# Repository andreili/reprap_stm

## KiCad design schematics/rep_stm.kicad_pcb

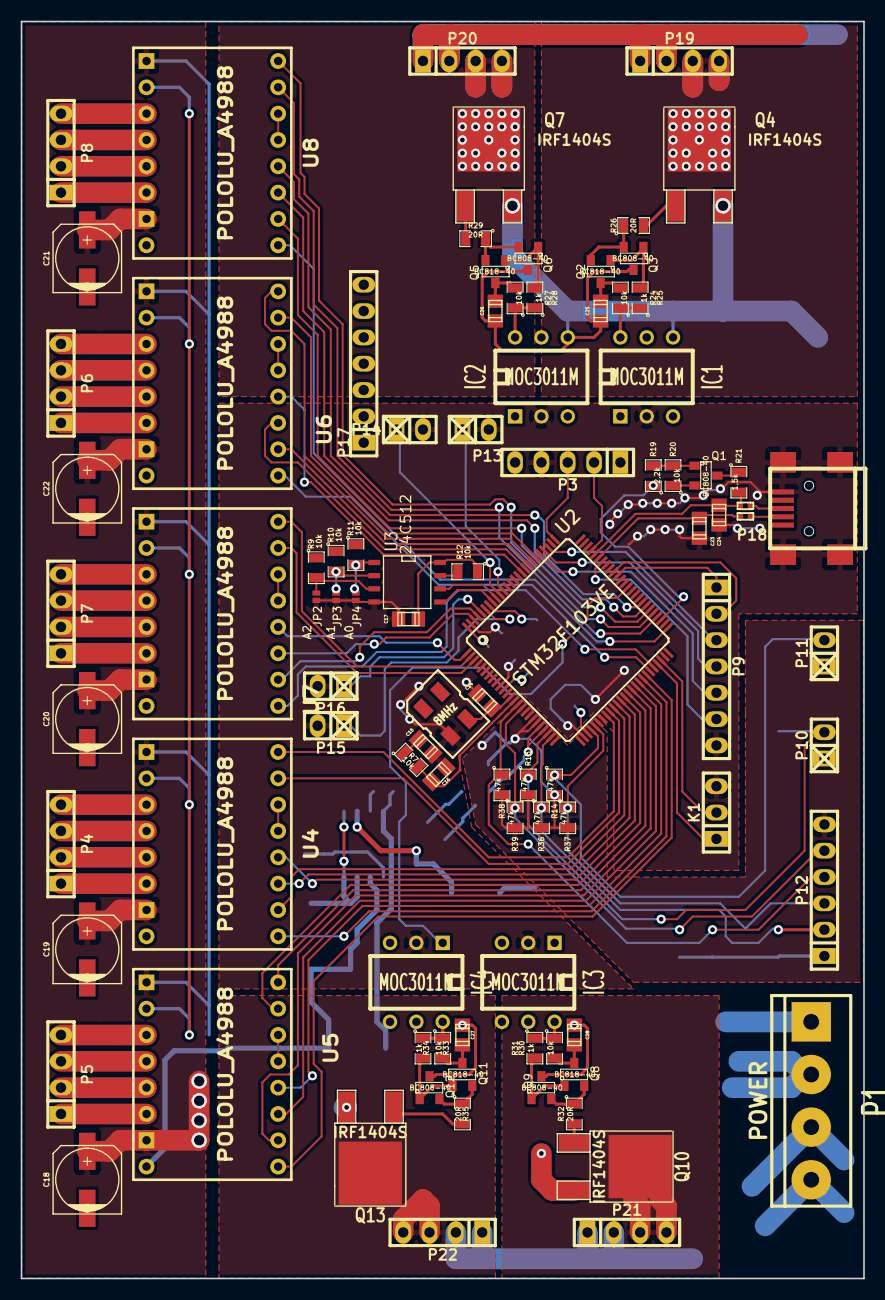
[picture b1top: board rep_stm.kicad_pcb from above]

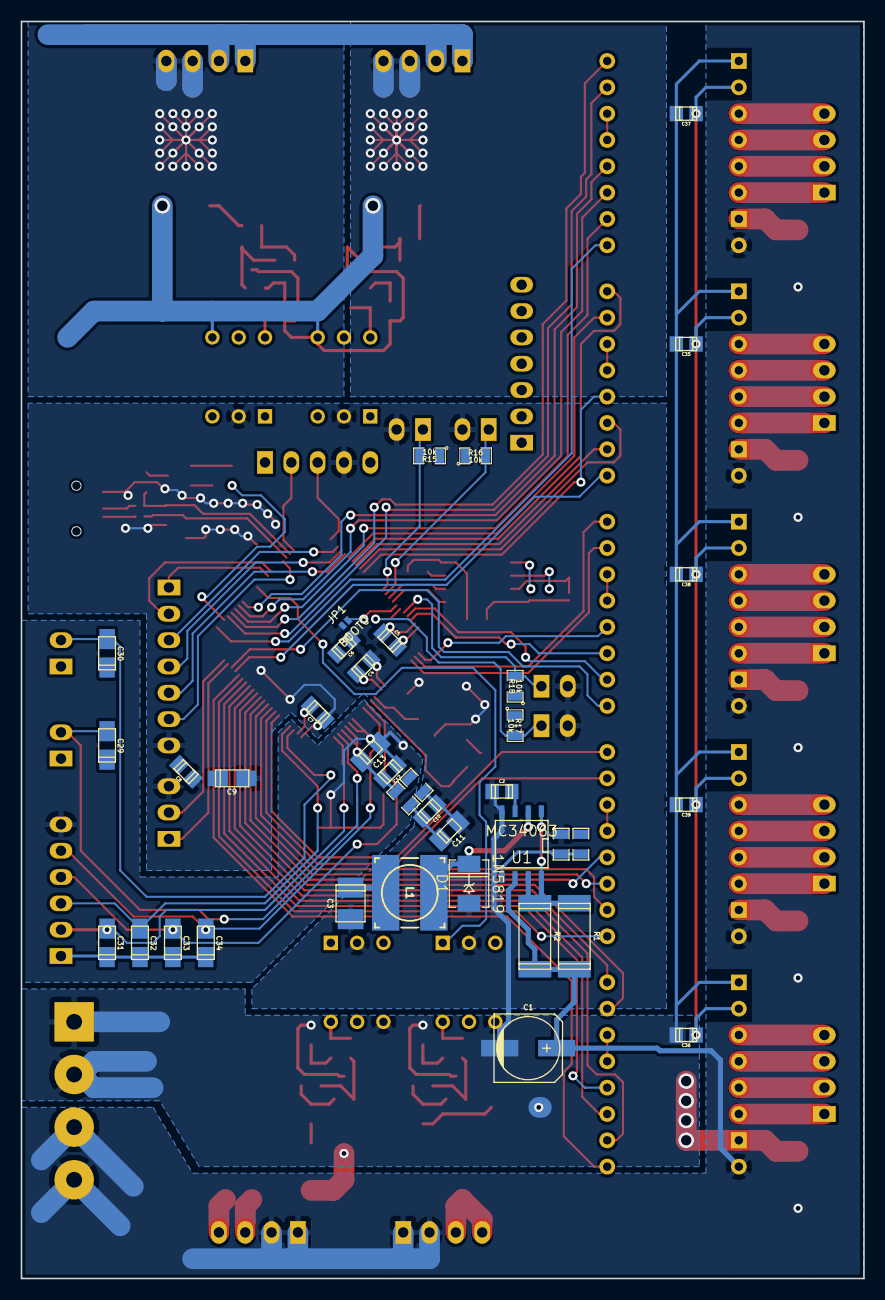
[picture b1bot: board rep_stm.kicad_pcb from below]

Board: 2 copper layers, 81.3 x 121.3 mm, 131 parts (38 on the bottom side), 129 nets.

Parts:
C1: 100u; c_elec_6.3x7.7
C2: 150pF; c_0805
C3: 47uF; c_tant_B
C4, C5, C6, C7, C8, C16, C17, C35, C36, C37, C38, C39: 100n; c_0805
C9: 4,7uF; c_tant_A
C10, C12, C15, C25, C26, C27, C28: 10n; c_0805
C11, C13: 1uF; c_tant_R
C14, C23, C24: 22pF; c_0805
C18, C19, C20, C21, C22: 100uFx25V; c_elec_6.3x7.7
C29, C30, C31, C32, C33, C34: 10uF; c_tant_A
D1: 1N5819; DO-214AC(SMA)
IC1, IC2, IC3, IC4: MOC3011M; DIP-6__300
JP1: BOOT0; S_JUMPER_2
JP2: A2; S_JUMPER_2
JP3: A1; S_JUMPER_2
JP4: A0; S_JUMPER_2
K1: UART; pin_socket_3
L1: 22uH; Inductor_CDRH6D28
L2, L3: 10uH; SM0805_Opendous
P1: POWER; bornier4
P3: PROG; pin_socket_5
P4: DRIVE 1; pin_socket_4
P5: DRIVE 2; pin_socket_4
P6: DRIVE 3; pin_socket_4
P7: DRIVE 4; pin_socket_4
P8: DRIVE 5; pin_socket_4
P9: DIGITAL OUT; pin_socket_7
P10: THERM1; pin_socket_2
P11: THERM2; pin_socket_2
P12: ANALOG IN; pin_socket_6
P13: END1; pin_socket_2
P14: END2; pin_socket_2
P15: END3; pin_socket_2
P16: END4; pin_socket_2
P17: DIGITAL INP; pin_socket_7
P18: USB-MINI-B; USB_MINI_B
P19: PWM 1; pin_socket_4
P20: PWM 2; pin_socket_4
P21: PWM 3; pin_socket_4
P22: PWM 4; pin_socket_4
Q1, Q3, Q6, Q9, Q12: BC808-40; SOT23
Q2, Q5, Q8, Q11: BC818-40; SOT23
Q4, Q7, Q10, Q13: IRF1404S; DPAK2
R1, R2: 0,47; r_2512
R5: 1,2k; SM0805_Opendous
R6: 2k; SM0805_Opendous
R7, R9, R10, R11, R12, R15, R16, R17, R18, R20, R24, R27, R30, R33: 10k; SM0805
R13, R14, R36, R37, R38, R39: 47k; SM0805
R19: 2,2k; SM0805
R21: 1,5k; SM0805
R22, R23: 33R; SM0402_Opendous
R25, R28, R31, R34: 1k; SM0805
R26, R29, R32, R35: 20R; SM0805
U1: MC34063; SO8N
U2: STM32F103VE; LQFP100
U3: 24C512; SO8N
U4, U5, U6, U7, U8: POLOLU_A4988; SWDIP8_.6W
X1: 8MHz; Crystal_7x5mm

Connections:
+12V: C1.1, C18.2, C19.2, C20.2, C21.2, C22.2, C25.1, C26.1, C27.1, C28.1, P1.3, P1.4, P19.1, P19.2, P20.1, P20.2, P21.1, P21.2, P22.1, P22.2, Q2.3, Q5.3, Q8.3, Q11.3, R1.1, R2.1, R24.2, R27.2, R30.2, R33.2, U1.6, U4.8, U5.8, U6.8, U7.8, U8.8
AIN1: C29.2, P10.2, R13.1, U2.23
AIN2: C31.2, P12.2, R36.1, U2.24
AIN3: C30.2, P11.2, R14.1, U2.29
AIN4: C32.2, P12.3, R37.1, U2.30
AIN5: C33.2, P12.4, R38.1, U2.15
AIN6: C34.2, P12.5, R39.1, U2.16
BOOT0: JP1.2, U2.94
DM: C23.1, R22.1, U2.70
DP: C24.1, R21.2, R23.1, U2.71
DR4MS2: U2.1, U7.12
Dr1Dir: U2.33, U4.16
Dr1Enable: U2.43, U4.9
Dr1MS0: U2.35, U4.10
Dr1MS1: U2.36, U4.11
Dr1MS2: U2.37, U4.12
Dr1Step: U2.34, U4.15
Dr2Dir: U2.39, U5.16
Dr2Enable: U2.44, U5.9
Dr2MS0: U2.40, U5.10
Dr2MS1: U2.41, U5.11
Dr2MS2: U2.42, U5.12
Dr2Step: U2.38, U5.15
Dr3Dir: U2.82, U6.16
Dr3Enable: U2.45, U6.9
Dr3MS0: U2.83, U6.10
Dr3MS1: U2.84, U6.11
Dr3MS2: U2.85, U6.12
Dr3Step: U2.81, U6.15
Dr4Dir: U2.2, U7.16
Dr4Enable: U2.46, U7.9
Dr4MS0: U2.97, U7.10
Dr4MS1: U2.98, U7.11
Dr4Step: U2.3, U7.15
Dr5Dir: U2.55, U8.16
Dr5Enable: U2.51, U8.9
Dr5MS0: U2.56, U8.10
Dr5MS1: U2.57, U8.11
Dr5MS2: U2.58, U8.12
Dr5Step: U2.54, U8.15
I2C_SCL: U2.92, U3.6
I2C_SDA: U2.93, U3.5
IN1: P13.1, R15.2, U2.90
IN2: P14.1, R16.2, U2.91
IN3: P15.1, R17.2, U2.95
IN4: P16.1, R18.2, U2.96
IN6: P17.2, U2.88
IN7: P17.3, U2.4, U2.17
IN8: P17.4, U2.5, U2.18
IN9: P17.5, U2.25
IN10: P17.6, U2.26
unnamed: JP4.2, R11.2, U3.1
unnamed: JP2.2, R9.2, U3.3
unnamed: JP3.2, R10.2, U3.2
unnamed: U8.13, U8.14
unnamed: U7.13, U7.14
unnamed: U6.13, U6.14
unnamed: R12.2, U3.7
unnamed: Q1.1, R19.2, R20.2
unnamed: U5.13, U5.14
unnamed: U4.13, U4.14
unnamed: Q10.1, R32.2
unnamed: Q13.1, R35.2
unnamed: Q8.1, Q9.1, R31.2
unnamed: R1.2, R2.2, U1.1, U1.7, U1.8
unnamed: C2.1, U1.3
unnamed: Q5.2, Q6.2, R29.1
unnamed: P6.4, U6.3
unnamed: P6.3, U6.4
unnamed: P5.1, U5.6
unnamed: P5.2, U5.5
unnamed: P5.3, U5.4
unnamed: P5.4, U5.3
unnamed: P7.1, U7.6
unnamed: P7.2, U7.5
unnamed: P7.3, U7.4
unnamed: P7.4, U7.3
unnamed: P6.1, U6.6
unnamed: P6.2, U6.5
unnamed: P4.1, U4.6
unnamed: P4.2, U4.5
unnamed: P4.3, U4.4
unnamed: P4.4, U4.3
unnamed: P8.1, U8.6
unnamed: P8.2, U8.5
unnamed: P8.3, U8.4
unnamed: P8.4, U8.3
unnamed: Q8.2, Q9.2, R32.1
unnamed: IC4.6, R33.1, R34.1
unnamed: Q11.1, Q12.1, R34.2
unnamed: IC3.6, R30.1, R31.1
unnamed: Q2.2, Q3.2, R26.1
unnamed: IC2.6, R27.1, R28.1
unnamed: Q5.1, Q6.1, R28.2
unnamed: Q11.2, Q12.2, R35.1
unnamed: IC1.6, R24.1, R25.1
unnamed: Q2.1, Q3.1, R25.2
unnamed: D1.2, L1.1, U1.2
unnamed: R5.1, R6.1, U1.5
unnamed: Q7.1, R29.2
unnamed: P18.3, R23.2
unnamed: P18.2, R22.2
unnamed: Q1.3, R21.1
unnamed: Q4.1, R26.2
NRST: C16.1, P3.1, R7.2, U2.14
OSC_OUT: C14.1, U2.13, X1.3
OUT1: P9.1, U2.65
OUT2: P9.2, U2.66
OUT3: P9.3, U2.78
OUT4: P9.4, U2.79
OUT5: P9.5, U2.80
OUT6: P9.6, U2.69
PWM1: IC1.1, U2.59
PWM1OUT: P19.3, P19.4, Q4.2
PWM2: IC2.1, U2.60
PWM2OUT: P20.3, P20.4, Q7.2
PWM3: IC3.1, U2.61
PWM3OUT: P21.3, P21.4, Q10.2
PWM4: IC4.1, U2.62
PWM4OUT: P22.3, P22.4, Q13.2
SWCLK: P3.3, U2.76
SWDIO: P3.2, U2.72
SlaveRX: K1.2, U2.48
SlaveTX: K1.1, U2.47
USBEN: R19.1, U2.53
VCOM: C1.2, C2.2, C3.2, C4.2, C5.2, C6.2, C7.2, C8.2, C9.2, C10.2, C11.2, C14.2, C15.2, C16.2, C17.2, C18.1, C19.1, C20.1, C21.1, C22.1, C23.2, C24.2, C25.2, C26.2, C27.2, C28.2, C35.1, C36.1, C37.1, C38.1, C39.1, D1.1, IC1.2, IC1.4, IC2.2, IC2.4, IC3.2, IC3.4, IC4.2, IC4.4, JP1.1, JP2.1, JP3.1, JP4.1, K1.3, L3.1, P1.1, P1.2, P3.4, P9.7, P13.2, P14.2, P15.2, P16.2, P17.7, P18.5, P18.6, P18.7, P18.8, P18.9, Q3.3, Q4.3, Q6.3, Q7.3, Q9.3, Q10.3, Q12.3, Q13.3, R5.2, U1.4, U2.10, U2.27, U2.49, U2.74, U2.99, U3.4, U4.1, U4.7, U5.1, U5.7, U6.1, U6.7, U7.1, U7.7, U8.1, U8.7, X1.2
VDD: C3.1, C4.1, C5.1, C6.1, C7.1, C8.1, C9.1, C10.1, C11.1, C15.1, C17.1, C35.2, C36.2, C37.2, C38.2, C39.2, L1.2, L2.1, P3.5, Q1.2, R6.2, R7.1, R9.1, R10.1, R11.1, R12.1, R15.1, R16.1, R17.1, R18.1, R20.1, U2.11, U2.28, U2.50, U2.75, U2.100, U3.8, U4.2, U5.2, U6.2, U7.2, U8.2, X1.4
VREF+: C12.1, C13.1, C29.1, C30.1, C31.1, C32.1, C33.1, C34.1, L2.2, P10.1, P11.1, P12.1, U2.21, U2.22
VREF-: C12.2, C13.2, L3.2, P12.6, R13.2, R14.2, R36.2, R37.2, R38.2, R39.2, U2.19, U2.20

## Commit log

2014-11-09 :circus_tent: Added .gitattributes & .gitignore files
2014-11-09 Base
2014-11-09 Drawing schematics
2014-11-09 Change IO
2014-11-09 Unfinished drawing...
2014-11-10 Fixed schematics
2014-11-10 Start drawing a PCB
2014-11-10 Merged with not-standart library
2014-11-11 Continue drawing a PCB
2014-11-12 Update PCB, Starting firmware
2014-11-12 Update firmware
